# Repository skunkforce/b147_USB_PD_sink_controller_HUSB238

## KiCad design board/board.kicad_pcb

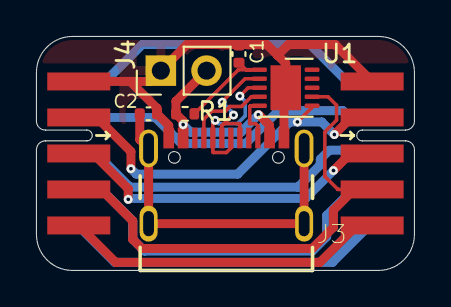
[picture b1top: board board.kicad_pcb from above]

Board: 2 copper layers, 21.0 x 13.0 mm, 9 parts (1 on the bottom side), 17 nets.

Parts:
C1: 1uF; C_0402_1005Metric
C2: 100pF; C_0402_1005Metric
J1: 001_I2C; on_edge_2x05_host
J2: 001_I2C; on_edge_2x05_device
J3: USB4105-GF-A; GCT_USB4105-GF-A
J4: Conn_01x02_Pin; PinHeader_1x02_P2.54mm_Vertical
LOGO1: Logo_Open_Hardware_Small; OSHW-Symbol_6.7x6mm_SilkScreen
R1: 10R; R_0402_1005Metric
U1: HUSB238; DFN-10-1EP_3x3mm_P0.5mm_EP1.7x2.5mm

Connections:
/USB_PD/CC1: J3.A5 (CC1), U1.4 (CC1)
/USB_PD/CC2: J3.B5 (CC2), U1.5 (CC2)
/USB_PD/D+: J3.A6 (DP1), J3.B6 (DP2), U1.2 (D+)
/USB_PD/D-: J3.A7 (DN1), J3.B7 (DN2), U1.3 (D-)
/USB_PD/SCL: J1.4 (SCL), J2.4 (SCL), U1.7 (SCL)
/USB_PD/SDA: J1.2 (SDA), J2.2 (SDA), U1.6 (SDA)
/USB_PD/VBUS: J3.A4/B9 (VBUS), J3.B4/A9 (VBUS), J4.2, R1.1
GND: C1.2, C2.2, J1.1 (GND), J2.1 (GND), J3.A1/B12 (GND), J3.B1/A12 (GND), J4.1, U1.11 (GND)
unnamed: C2.1, J3.G1 (SCHIELD), J3.G2 (SCHIELD), J3.G3 (SCHIELD), J3.G4 (SCHIELD)
unnamed: J1.9 (3.3V), J2.9 (3.3V)
unnamed: J1.10 (5V), J2.10 (5V)
unnamed: J1.6 (CS/EN), J2.6 (CS/EN)
unnamed: J1.5 (INT), J2.5 (INT)
unnamed: J1.3 (N/C), J2.3 (N/C)
unnamed: J1.7 (status), J2.7 (status)
unnamed: J1.8 (~RESET), J2.8 (~RESET)
unnamed: C1.1, R1.2, U1.1 (VIN)

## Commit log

2024-01-14 initial b147
